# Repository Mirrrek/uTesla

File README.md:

# uTesla

uTesla (_microTesla_) is a small in size, but definitely impressive Tesla coil. It's core drive circuitry is inspired by [Tefatronix](https://tefatronix.g6.cz/)'s (a fellow Czech!) SSTC IV. The driver runs on 24V (up to 28V for those feeling adventurous) and is controlled by an ATmega328P microcontroller with an SD card slot.

## Hardware

uTesla consists of three main components:

### The driver board

Schematics for this board are available in the [schematic](https://github.com/Mirrrek/uTesla/tree/main/schematic) folder.

The board is intended to be installed with the components facing down. The other side of the PCB serves as a shield from the electromagnetic radiation produced by the coil.

Additional shielding may be required, such as covering the ATmega328P with copper tape (make sure not to short anything out!) connected to the grounding pads present throughout the board.

### The primary coil

Similarly to Tefatronix's design, a 16 pin ribbon cable connected in a A-24V, 24V-B, A-24V, 24V-B pattern serves as the primary coil.

The primary diameter should be around 2cm larger than the secondary coil.

### The secondary coil

Again, this closely follows Tefatronix's design. The secondary consists of a ~3.5cm diameter PVC pipe with around 500 turns of 0.1mm enameled copper wire wound around it.

The resonance can be maximized using tuning capacitors, so the secondary coil doesn't have to match exactly.

## Software

Software for uTesla is a work in progress.

## Expansion

For simple changes (e.g. adding an LCD screen with some buttons) the board has an IO header with 10 pins available.

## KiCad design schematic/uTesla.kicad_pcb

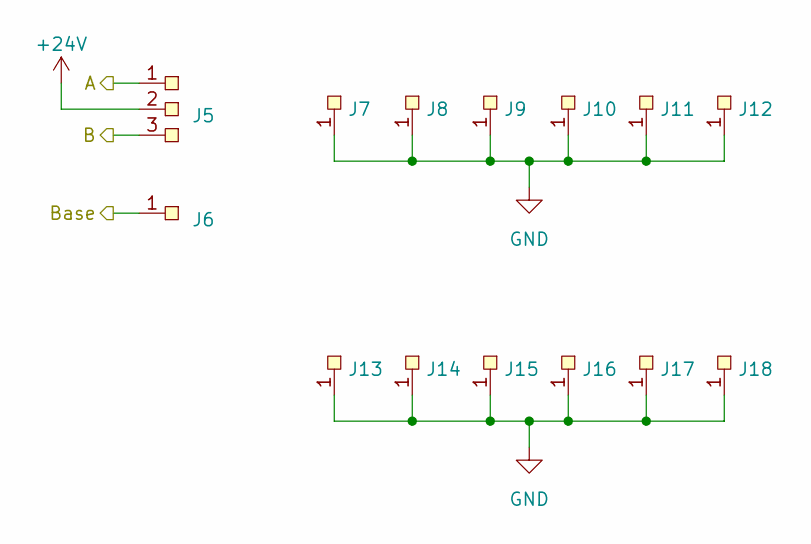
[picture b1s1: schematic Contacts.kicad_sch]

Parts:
J5: SolderPad-3pin
J6, J7, J8, J9, J10, J11, J12, J13, J14, J15, J16, J17, J18: SolderPad-1pin

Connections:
+24V: J5.2; also elsewhere on the board
/Contacts/A: J5.1; also elsewhere on the board
/Contacts/B: J5.3; also elsewhere on the board
/Contacts/Base: J6.1; also elsewhere on the board
GND: J7.1, J8.1, J9.1, J10.1, J11.1, J12.1, J13.1, J14.1, J15.1, J16.1, J17.1, J18.1; also elsewhere on the board

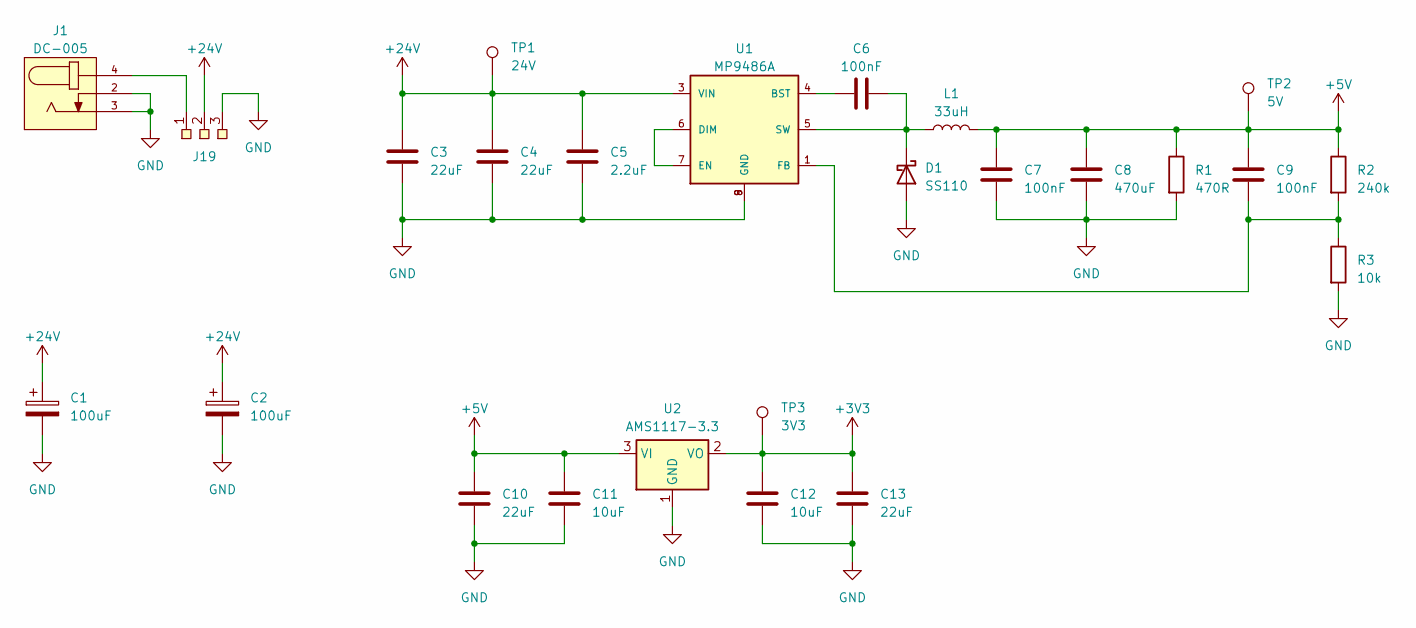
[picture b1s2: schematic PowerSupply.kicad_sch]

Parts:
C1, C2: 100uF; CP_Radial_D8.0mm_P3.80mm
C3, C4, C10, C13: 22uF; C_0603_1608Metric
C5: 2.2uF; C_0603_1608Metric
C6, C7, C9: 100nF; C_0603_1608Metric
C8: 470uF; C_0603_1608Metric
C11, C12: 10uF; C_0603_1608Metric
D1: SS110; D_SMA
J1: DC-005; NINIGI_DC-005
J19: SolderPad-3pin
L1: 33uH; L_Toroid_Vertical_L26.7mm_W14.0mm_P10.16mm_Pulse_D
R1: 470R; R_0603_1608Metric
R2: 240k; R_0603_1608Metric
R3: 10k; R_0603_1608Metric
TP1: 24V; TestPoint_Pad_D2.0mm
TP2: 5V; TestPoint_Pad_D2.0mm
TP3: 3V3; TestPoint_Pad_D2.0mm
U1: MP9486A; SOIC-8EP
U2: AMS1117-3.3; SOT-223-3_TabPin2

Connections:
+3V3: C12.1, C13.1, TP3.1, U2.2 (VO); also elsewhere on the board
+5V: C7.1, C8.1, C9.1, C10.1, C11.1, L1.2, R1.1, R2.1, TP2.1, U2.3 (VI); also elsewhere on the board
+24V: C1.1, C2.1, C3.1, C4.1, C5.1, J19.2, TP1.1, U1.3 (VIN); also elsewhere on the board
GND: C1.2, C2.2, C3.2, C4.2, C5.2, C7.2, C8.2, C10.2, C11.2, C12.2, C13.2, D1.2 (A), J1.2, J1.3, J19.3, R1.2, R3.2, U1.8 (GND), U1.9 (GND), U2.1 (GND); also elsewhere on the board
unnamed: C6.2, D1.1 (K), L1.1, U1.5 (SW)
unnamed: J1.4, J19.1
unnamed: C6.1, U1.4 (BST)
unnamed: U1.6 (DIM), U1.7 (EN)
unnamed: C9.2, R2.2, R3.1, U1.1 (FB)

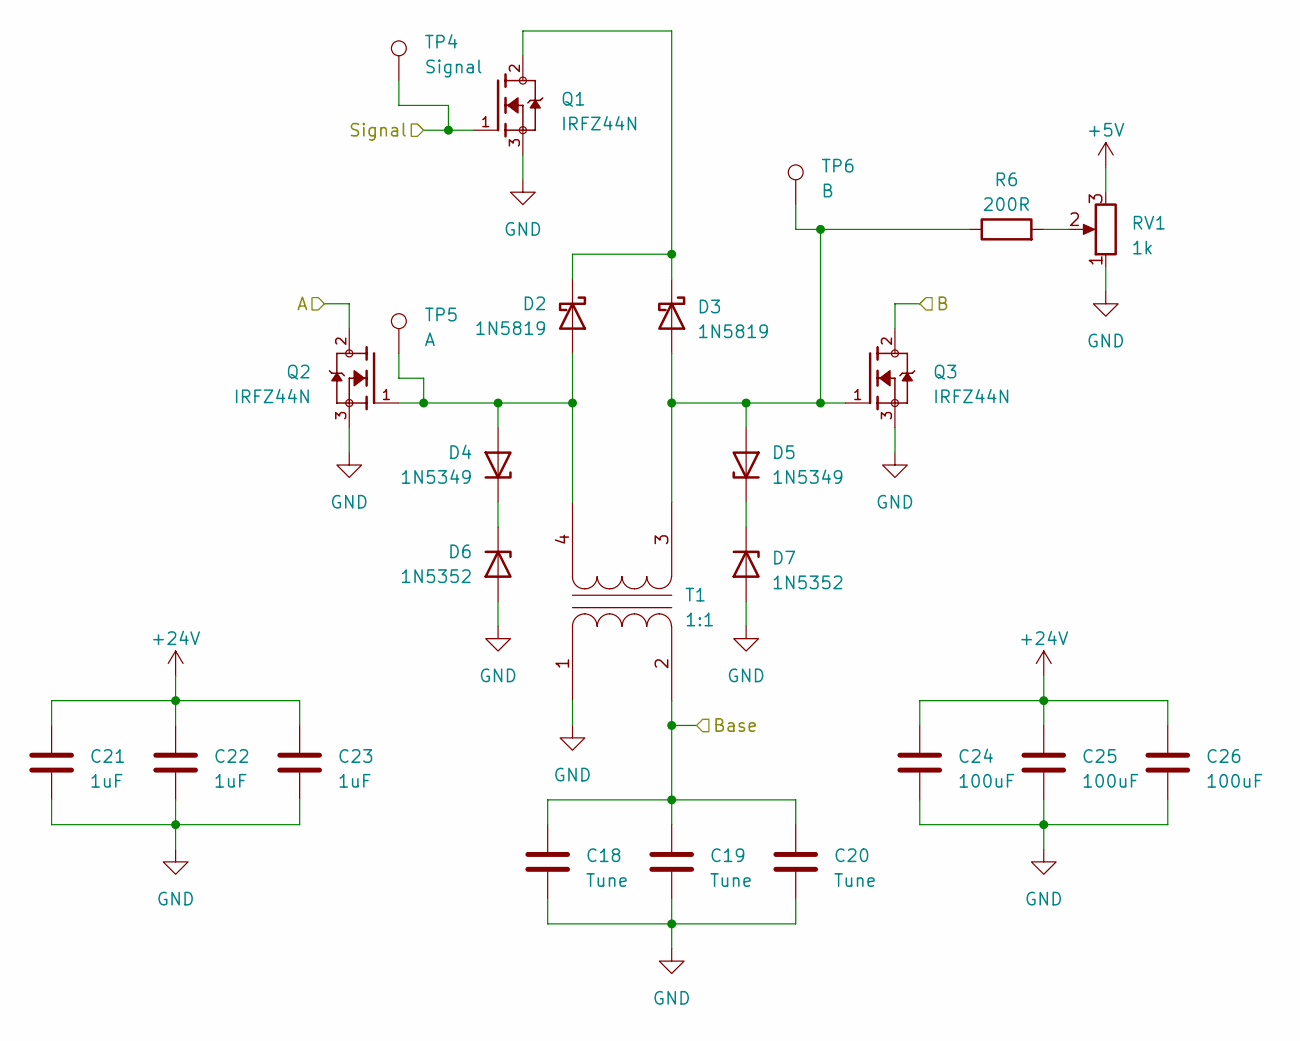
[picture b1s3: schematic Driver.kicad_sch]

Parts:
C18, C19, C20: Tune; C_0603_1608Metric
C21, C22, C23: 1uF; C_0603_1608Metric
C24, C25, C26: 100uF; CP_Radial_D8.0mm_P3.80mm
D2, D3: 1N5819; D_DO-41_SOD81_P10.16mm_Horizontal
D4, D5: 1N5349; D_DO-41_SOD81_P10.16mm_Horizontal
D6, D7: 1N5352; D_DO-41_SOD81_P10.16mm_Horizontal
Q1, Q2, Q3: IRFZ44N; TO254P1016X419X2286-3; PARTREV 09/21/10
R6: 200R; R_0603_1608Metric
RV1: 1k; Potentiometer_Runtron_RM-065_Vertical
T1: 1:1; Transformer_Toroid_Horizontal_D9.0mm_Amidon-T30
TP4: Signal; TestPoint_Pad_D2.0mm
TP5: A; TestPoint_Pad_D2.0mm
TP6: B; TestPoint_Pad_D2.0mm

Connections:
+5V: RV1.3; also elsewhere on the board
+24V: C21.1, C22.1, C23.1, C24.1, C25.1, C26.1; also elsewhere on the board
/Contacts/A: Q2.2; also elsewhere on the board
/Contacts/B: Q3.2; also elsewhere on the board
/Contacts/Base: C18.1, C19.1, C20.1, T1.2 (AB); also elsewhere on the board
/Driver/Signal: Q1.1, TP4.1; also elsewhere on the board
GND: C18.2, C19.2, C20.2, C21.2, C22.2, C23.2, C24.2, C25.2, C26.2, D6.2 (A), D7.2 (A), Q1.3, Q2.3, Q3.3, RV1.1, T1.1 (AA); also elsewhere on the board
unnamed: D2.2 (A), D4.2 (A), Q2.1, T1.4 (SB), TP5.1
unnamed: D2.1 (K), D3.1 (K), Q1.2
unnamed: D3.2 (A), D5.2 (A), Q3.1, R6.1, T1.3 (SA), TP6.1
unnamed: D4.1 (K), D6.1 (K)
unnamed: D5.1 (K), D7.1 (K)
unnamed: R6.2, RV1.2

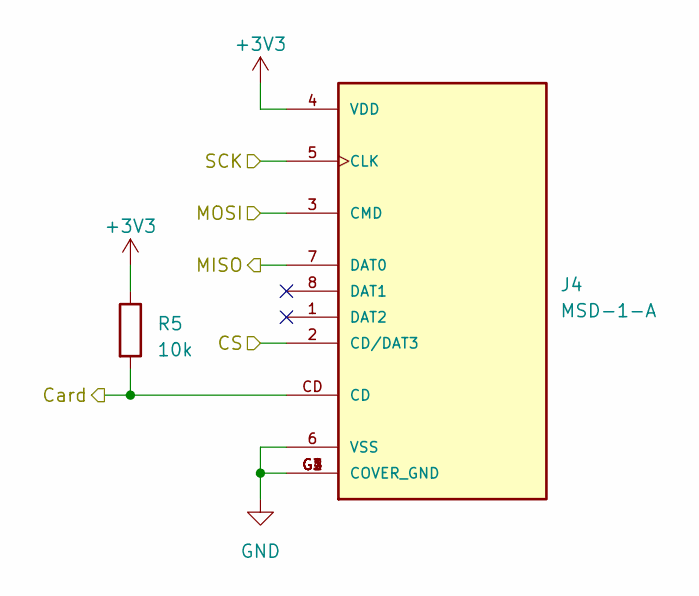
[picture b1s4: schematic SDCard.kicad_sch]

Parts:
J4: MSD-1-A; CUI_MSD-1-A; PARTREV 1.0
R5: 10k; R_0603_1608Metric

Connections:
+3V3: J4.4 (VDD), R5.1; also elsewhere on the board
/Microcontroller/CS: J4.2 (CD/DAT3); also elsewhere on the board
/Microcontroller/Card: J4.CD, R5.2; also elsewhere on the board
/Microcontroller/MISO: J4.7 (DAT0); also elsewhere on the board
/Microcontroller/MOSI: J4.3 (CMD); also elsewhere on the board
/Microcontroller/SCK: J4.5 (CLK); also elsewhere on the board
GND: J4.6 (VSS), J4.G1 (COVER_GND), J4.G2 (COVER_GND), J4.G3 (COVER_GND), J4.G4 (COVER_GND); also elsewhere on the board

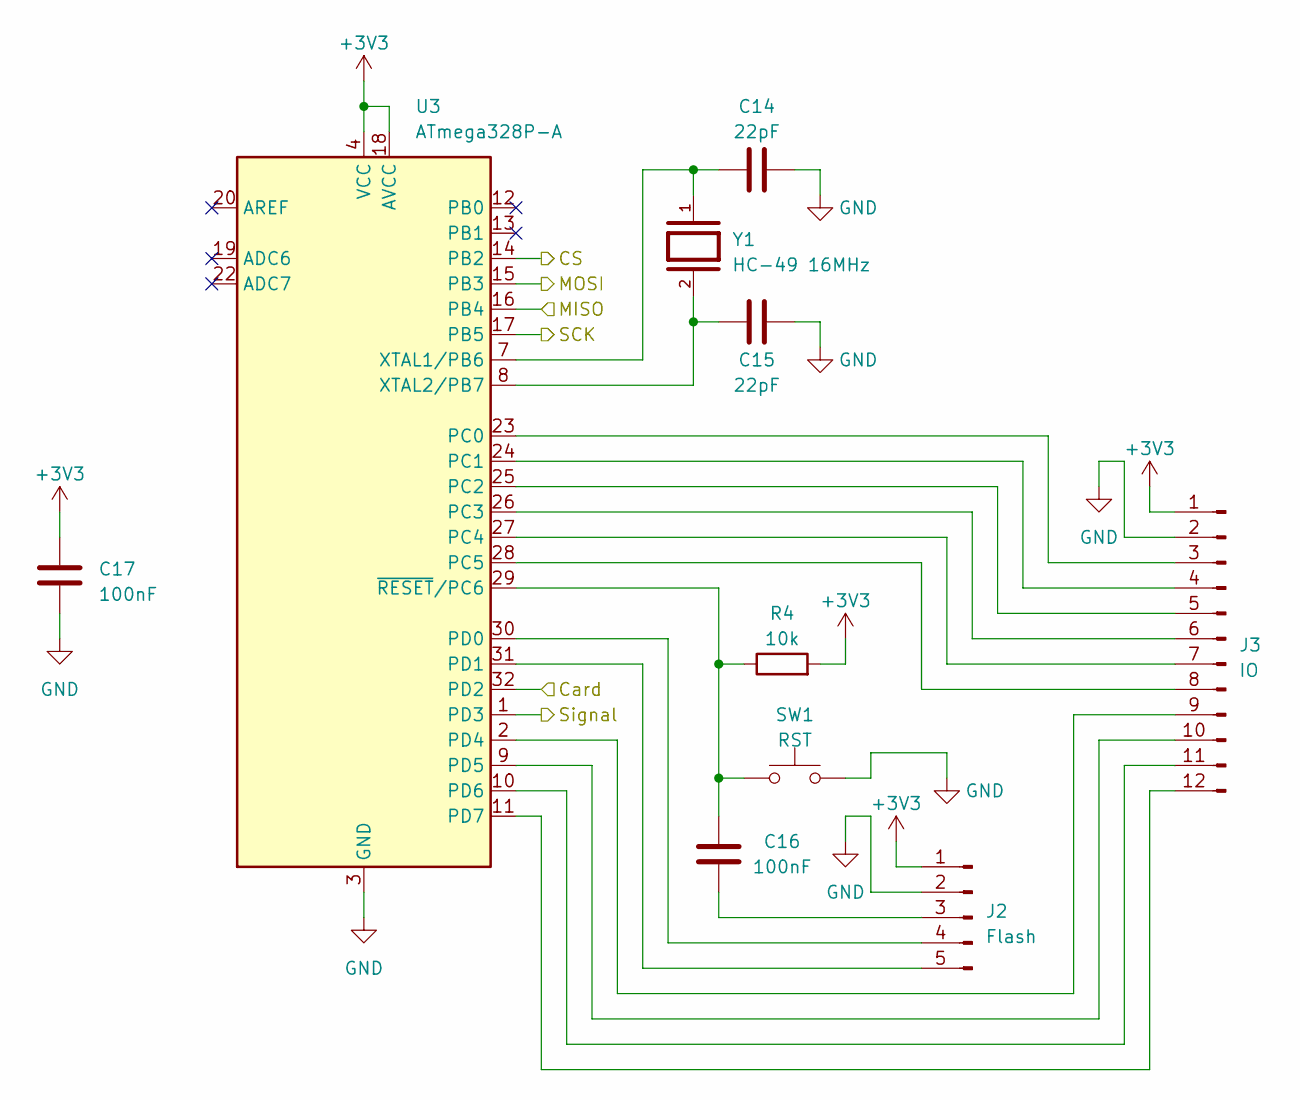
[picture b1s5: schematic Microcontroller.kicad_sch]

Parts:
C14, C15: 22pF; C_0603_1608Metric
C16, C17: 100nF; C_0603_1608Metric
J2: Flash; PinHeader_1x05_P2.54mm_Vertical
J3: IO; PinHeader_1x12_P2.54mm_Vertical
R4: 10k; R_0603_1608Metric
SW1: RST; SW_PUSH_6mm
U3: ATmega328P-A; TQFP-32_7x7mm_P0.8mm
Y1: HC-49 16MHz; XTAL_HC49P488W43L1150T466H350; PARTREV 1.0

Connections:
+3V3: C17.1, J2.1, J3.1, R4.2, U3.4 (VCC), U3.6 (VCC), U3.18 (AVCC); also elsewhere on the board
/Driver/Signal: U3.1 (PD3); also elsewhere on the board
/Microcontroller/CS: U3.14 (PB2); also elsewhere on the board
/Microcontroller/Card: U3.32 (PD2); also elsewhere on the board
/Microcontroller/MISO: U3.16 (PB4); also elsewhere on the board
/Microcontroller/MOSI: U3.15 (PB3); also elsewhere on the board
/Microcontroller/SCK: U3.17 (PB5); also elsewhere on the board
GND: C14.2, C15.2, C17.2, J2.2, J3.2, SW1.2, U3.3 (GND), U3.5 (GND), U3.21 (GND); also elsewhere on the board
unnamed: C16.1, J2.3
unnamed: J2.4, U3.30 (PD0)
unnamed: J2.5, U3.31 (PD1)
unnamed: J3.3, U3.23 (PC0)
unnamed: J3.4, U3.24 (PC1)
unnamed: J3.5, U3.25 (PC2)
unnamed: J3.6, U3.26 (PC3)
unnamed: J3.7, U3.27 (PC4)
unnamed: J3.8, U3.28 (PC5)
unnamed: J3.9, U3.2 (PD4)
unnamed: J3.10, U3.9 (PD5)
unnamed: J3.11, U3.10 (PD6)
unnamed: J3.12, U3.11 (PD7)
unnamed: C14.1, U3.7 (XTAL1/PB6), Y1.1
unnamed: C15.1, U3.8 (XTAL2/PB7), Y1.2
unnamed: C16.2, R4.1, SW1.1, U3.29 (~RESET/PC6)

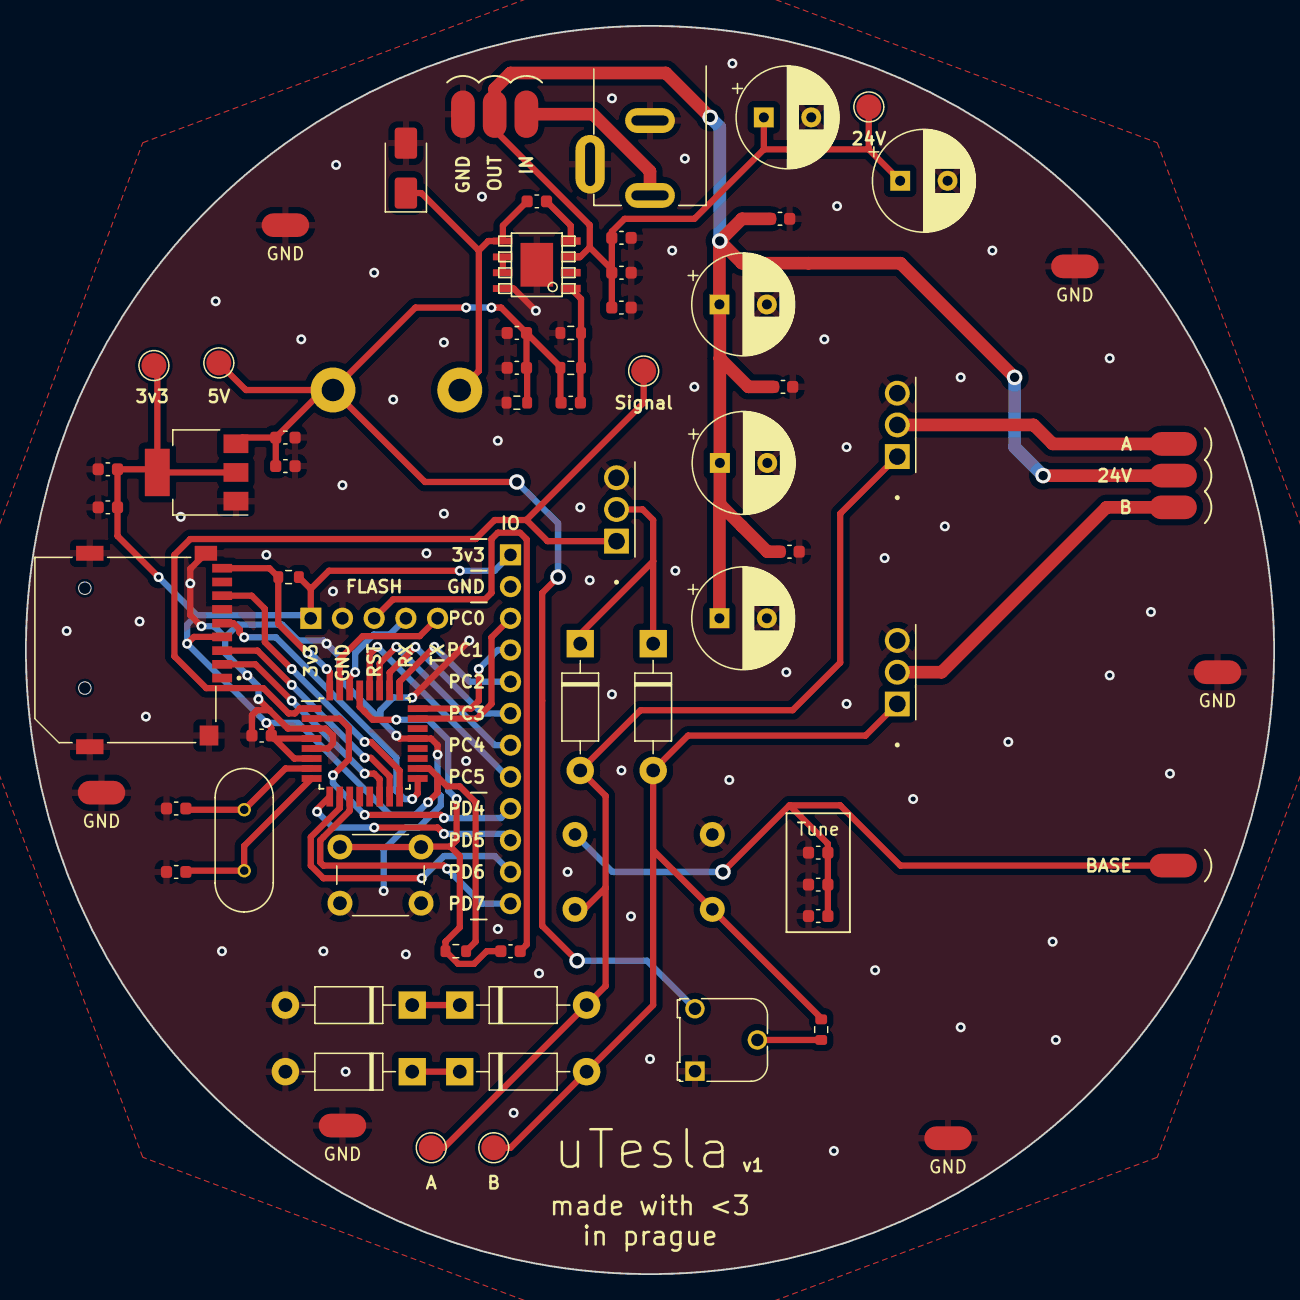
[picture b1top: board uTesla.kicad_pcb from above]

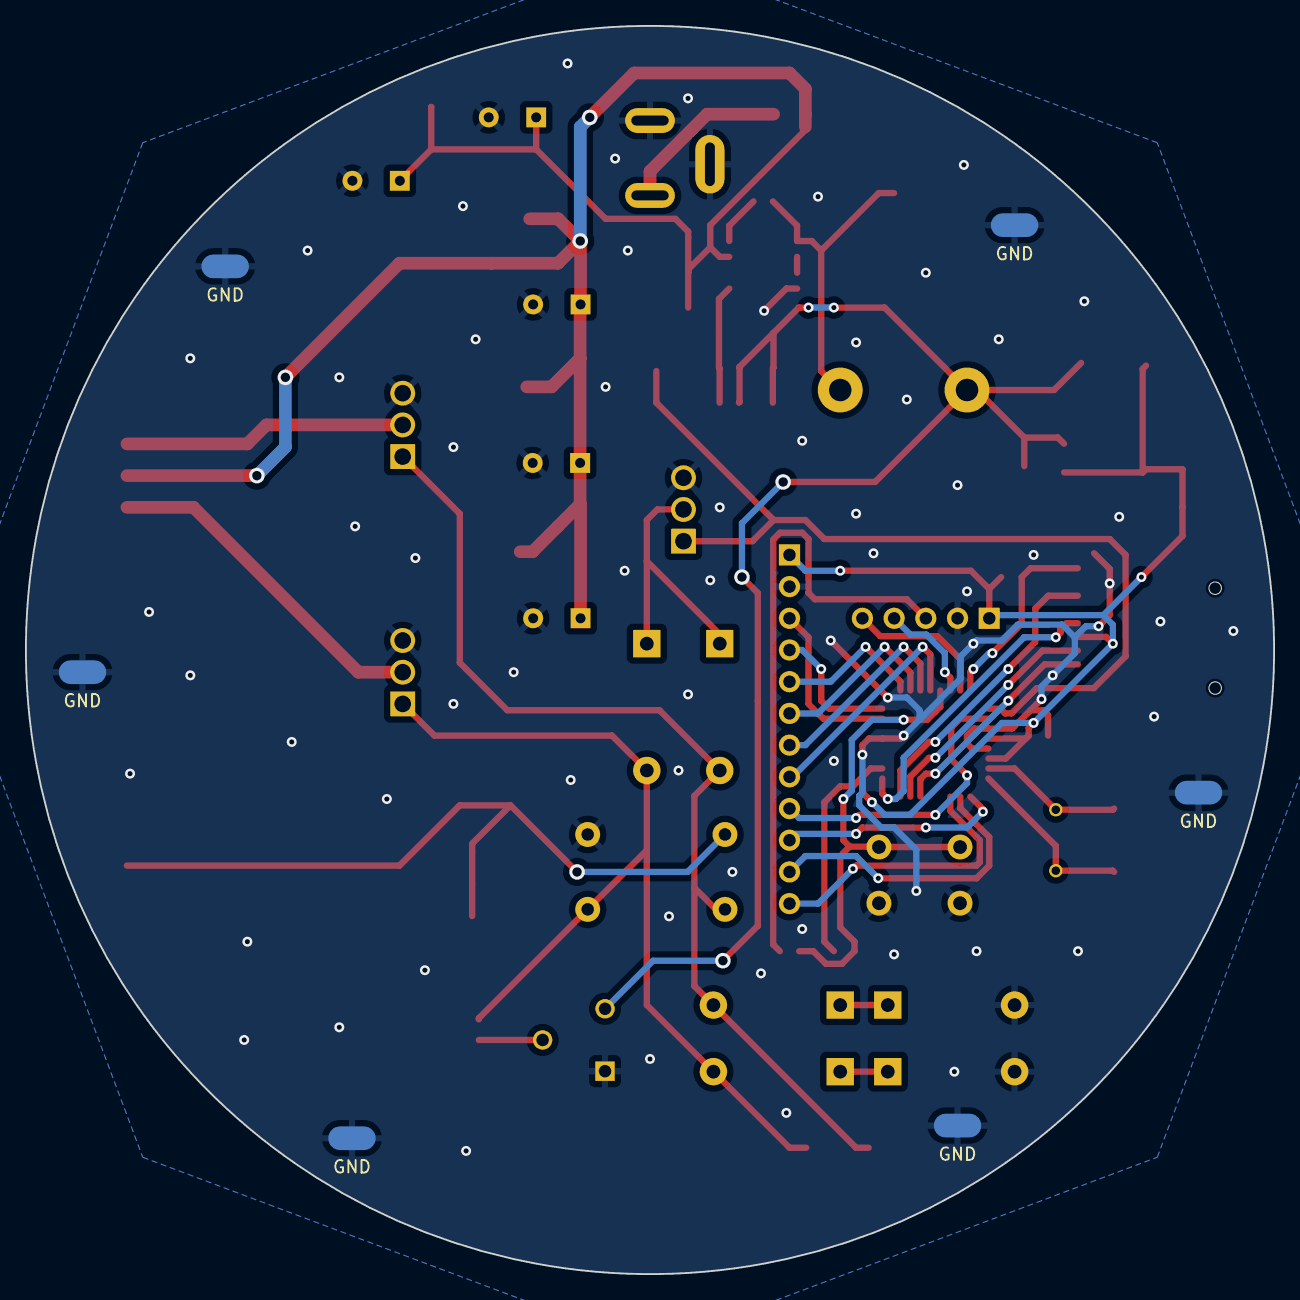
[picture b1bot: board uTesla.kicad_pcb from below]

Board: 2 copper layers, 100.0 x 100.0 mm, 75 parts (6 on the bottom side), 40 nets.

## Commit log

2024-08-09 Initialize development environment
2024-08-09 Add README
2024-08-09 Make high level schematic
2024-08-09 Create power supply schematic
2024-08-10 Create microcontroller schematic
2024-08-10 Create SD card schematic
2024-08-10 Create driver schematic
2024-08-10 Create connector schematic
2024-08-10 Add test points to driver signals
2024-08-10 Decrease input decoupling capacitance
2024-08-10 Assign footprints
2024-08-10 Fix driver transformer footprint
2024-08-10 Add grounding solder pads
2024-08-10 Design PCB
2024-08-10 Add power switch
2024-08-10 Add silkscreen labels
2024-08-10 Generate gerber files
2024-08-11 Scale down PCB
